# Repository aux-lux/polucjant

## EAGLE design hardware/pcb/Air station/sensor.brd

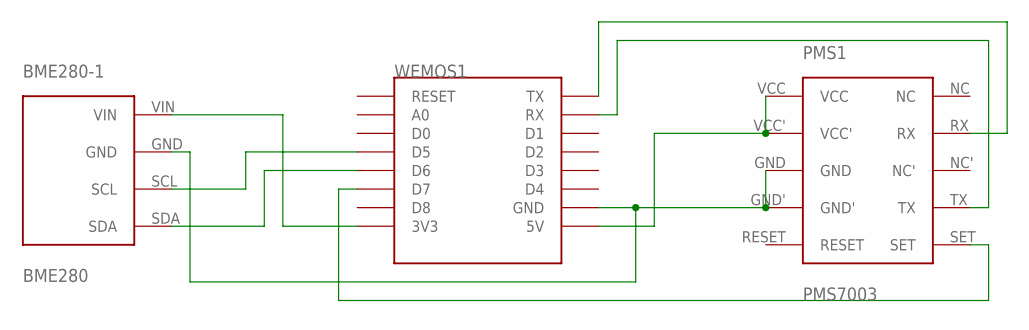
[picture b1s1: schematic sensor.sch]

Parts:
BME280-1: BME280
PMS1: PMS7003
WEMOS1: WEMOS-D1-MINI

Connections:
GND: BME280-1.GND, PMS1.GND, PMS1.GND', WEMOS1.GND
unnamed: BME280-1.SCL, WEMOS1.D5
unnamed: BME280-1.SDA, WEMOS1.D6
unnamed: BME280-1.VIN, WEMOS1.3V3
unnamed: PMS1.SET, WEMOS1.D7
unnamed: PMS1.VCC, PMS1.VCC', WEMOS1.5V
unnamed: PMS1.RX, WEMOS1.TX
unnamed: PMS1.TX, WEMOS1.RX

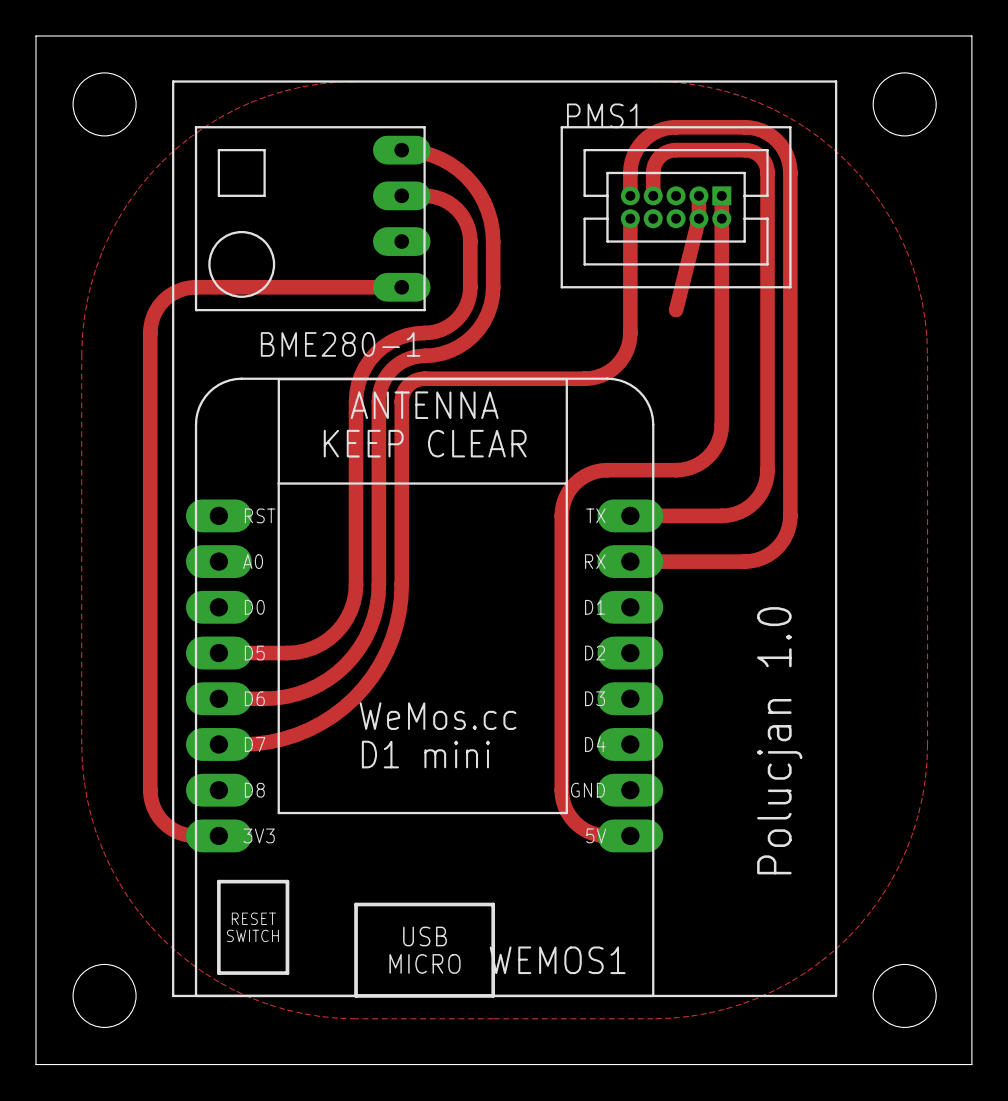
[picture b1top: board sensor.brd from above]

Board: 2 copper layers, 52.0 x 57.1 mm, 3 parts (0 on the bottom side), 8 nets.

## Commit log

2020-02-25 initial
2020-02-25 Bump mixin-deep from 1.3.1 to 1.3.2
    Bumps [mixin-deep](https://github.com/jonschlinkert/mixin-deep) from 1.3.1 to 1.3.2.
    - [Release notes](https://github.com/jonschlinkert/mixin-deep/releases)
    - [Commits](https://github.com/jonschlinkert/mixin-deep/compare/1.3.1...1.3.2)
2020-02-25 Bump extend from 3.0.1 to 3.0.2
    Bumps [extend](https://github.com/justmoon/node-extend) from 3.0.1 to 3.0.2.
    - [Release notes](https://github.com/justmoon/node-extend/releases)
    - [Changelog](https://github.com/justmoon/node-extend/blob/master/CHANGELOG.md)
    - [Commits](https://github.com/justmoon/node-extend/compare/v3.0.1...v3.0.2)
2020-02-25 cleanup
2020-08-20 Bump bcrypt from 3.0.8 to 5.0.0
    Bumps [bcrypt](https://github.com/kelektiv/node.bcrypt.js) from 3.0.8 to 5.0.0.
    - [Release notes](https://github.com/kelektiv/node.bcrypt.js/releases)
    - [Changelog](https://github.com/kelektiv/node.bcrypt.js/blob/master/CHANGELOG.md)
    - [Commits](https://github.com/kelektiv/node.bcrypt.js/compare/v3.0.8...v5.0.0)
2020-12-12 Bump ini from 1.3.5 to 1.3.8
    Bumps [ini](https://github.com/isaacs/ini) from 1.3.5 to 1.3.8.
    - [Release notes](https://github.com/isaacs/ini/releases)
    - [Commits](https://github.com/isaacs/ini/compare/v1.3.5...v1.3.8)
2021-01-21 Bump socket.io from 2.3.0 to 2.4.0
    Bumps [socket.io](https://github.com/socketio/socket.io) from 2.3.0 to 2.4.0.
    - [Release notes](https://github.com/socketio/socket.io/releases)
    - [Changelog](https://github.com/socketio/socket.io/blob/2.4.0/CHANGELOG.md)
    - [Commits](https://github.com/socketio/socket.io/compare/2.3.0...2.4.0)
2021-06-30 Bump socket.io-parser from 3.3.0 to 3.3.2
    Bumps [socket.io-parser](https://github.com/socketio/socket.io-parser) from 3.3.0 to 3.3.2.
    - [Release notes](https://github.com/socketio/socket.io-parser/releases)
    - [Changelog](https://github.com/socketio/socket.io-parser/blob/3.3.2/CHANGELOG.md)
    - [Commits](https://github.com/socketio/socket.io-parser/compare/3.3.0...3.3.2)
    ---
    updated-dependencies:
2021-08-04 Bump tar from 4.4.13 to 4.4.15
    Bumps [tar](https://github.com/npm/node-tar) from 4.4.13 to 4.4.15.
    - [Release notes](https://github.com/npm/node-tar/releases)
    - [Changelog](https://github.com/npm/node-tar/blob/main/CHANGELOG.md)
    - [Commits](https://github.com/npm/node-tar/compare/v4.4.13...v4.4.15)
    ---
    updated-dependencies:
2021-08-12 Bump path-parse from 1.0.6 to 1.0.7
    Bumps [path-parse](https://github.com/jbgutierrez/path-parse) from 1.0.6 to 1.0.7.
    - [Release notes](https://github.com/jbgutierrez/path-parse/releases)
    - [Commits](https://github.com/jbgutierrez/path-parse/commits/v1.0.7)
    ---
    updated-dependencies:
    - dependency-name: path-parse
2021-09-02 Bump tar from 4.4.13 to 4.4.19
    Bumps [tar](https://github.com/npm/node-tar) from 4.4.13 to 4.4.19.
    - [Release notes](https://github.com/npm/node-tar/releases)
    - [Changelog](https://github.com/npm/node-tar/blob/main/CHANGELOG.md)
    - [Commits](https://github.com/npm/node-tar/compare/v4.4.13...v4.4.19)
    ---
    updated-dependencies:
2022-02-13 Bump ajv from 6.12.0 to 6.12.6
    Bumps [ajv](https://github.com/ajv-validator/ajv) from 6.12.0 to 6.12.6.
    - [Release notes](https://github.com/ajv-validator/ajv/releases)
    - [Commits](https://github.com/ajv-validator/ajv/compare/v6.12.0...v6.12.6)
    ---
    updated-dependencies:
    - dependency-name: ajv
2022-04-09 Bump moment from 2.24.0 to 2.29.2
    Bumps [moment](https://github.com/moment/moment) from 2.24.0 to 2.29.2.
    - [Release notes](https://github.com/moment/moment/releases)
    - [Changelog](https://github.com/moment/moment/blob/develop/CHANGELOG.md)
    - [Commits](https://github.com/moment/moment/compare/2.24.0...2.29.2)
    ---
    updated-dependencies:
2022-07-07 Bump moment from 2.24.0 to 2.29.4
    Bumps [moment](https://github.com/moment/moment) from 2.24.0 to 2.29.4.
    - [Release notes](https://github.com/moment/moment/releases)
    - [Changelog](https://github.com/moment/moment/blob/develop/CHANGELOG.md)
    - [Commits](https://github.com/moment/moment/compare/2.24.0...2.29.4)
    ---
    updated-dependencies:
2022-11-09 Bump socket.io-parser from 3.3.0 to 3.3.3
    Bumps [socket.io-parser](https://github.com/socketio/socket.io-parser) from 3.3.0 to 3.3.3.
    - [Release notes](https://github.com/socketio/socket.io-parser/releases)
    - [Changelog](https://github.com/socketio/socket.io-parser/blob/main/CHANGELOG.md)
    - [Commits](https://github.com/socketio/socket.io-parser/compare/3.3.0...3.3.3)
    ---
    updated-dependencies:
2022-11-23 Bump engine.io and socket.io
    Bumps [engine.io](https://github.com/socketio/engine.io) to 3.6.1 and updates ancestor dependency [socket.io](https://github.com/socketio/socket.io). These dependencies need to be updated together.
    Updates `engine.io` from 3.4.0 to 3.6.1
    - [Release notes](https://github.com/socketio/engine.io/releases)
    - [Changelog](https://github.com/socketio/engine.io/blob/main/CHANGELOG.md)
    - [Commits](https://github.com/socketio/engine.io/compare/3.4.0...3.6.1)
    Updates `socket.io` from 2.3.0 to 2.5.0
2022-12-05 Bump decode-uri-component from 0.2.0 to 0.2.2
    Bumps [decode-uri-component](https://github.com/SamVerschueren/decode-uri-component) from 0.2.0 to 0.2.2.
    - [Release notes](https://github.com/SamVerschueren/decode-uri-component/releases)
    - [Commits](https://github.com/SamVerschueren/decode-uri-component/compare/v0.2.0...v0.2.2)
    ---
    updated-dependencies:
    - dependency-name: decode-uri-component
2022-12-07 Bump qs from 6.5.2 to 6.5.3
    Bumps [qs](https://github.com/ljharb/qs) from 6.5.2 to 6.5.3.
    - [Release notes](https://github.com/ljharb/qs/releases)
    - [Changelog](https://github.com/ljharb/qs/blob/main/CHANGELOG.md)
    - [Commits](https://github.com/ljharb/qs/compare/v6.5.2...v6.5.3)
    ---
    updated-dependencies:
2022-12-12 Bump express from 4.17.1 to 4.17.3
    Bumps [express](https://github.com/expressjs/express) from 4.17.1 to 4.17.3.
    - [Release notes](https://github.com/expressjs/express/releases)
    - [Changelog](https://github.com/expressjs/express/blob/master/History.md)
    - [Commits](https://github.com/expressjs/express/compare/4.17.1...4.17.3)
    ---
    updated-dependencies:
2023-01-24 Bump cookiejar from 2.1.2 to 2.1.4
    Bumps [cookiejar](https://github.com/bmeck/node-cookiejar) from 2.1.2 to 2.1.4.
    - [Release notes](https://github.com/bmeck/node-cookiejar/releases)
    - [Commits](https://github.com/bmeck/node-cookiejar/commits)
    ---
    updated-dependencies:
    - dependency-name: cookiejar
